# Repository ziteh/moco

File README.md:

# moco

|  SC1  | RD501 |
| :---: | :---: |
|  |  |

BLDC/PMSM motor controller/driver boards. [SC1 Demo video](https://youtu.be/PZ3AqAKdYeg)

- [SC1](/hardware/moco-sc1/): STSPIN32G4 + CSD88584Q5DC. Square PCB 40x40mm.
- [RD501](/hardware/moco-rd501/): DRV8301 + STM32G431. Square PCB 50x50mm.
- [RD321](/hardware/moco-rd321/): STSPIN32F0A + SiZ250DT. Square PCB 32x32mm.
- [OD501](/hardware/moco-od501/): DRV8323H + STM32G431. Round PCB Ø50mm.
- [OI401](/hardware/moco-oi401/): DRV8316C + STM32G431. Round PCB Ø40mm.
- [PG4](/hardware/moco-pg4/):  :construction: WIP.
- [BKD8316](/hardware/moco-bkd8316/): DRV8316 Breakout board

## Disclaimer & License

> [!WARNING]  
> None of the boards here are guaranteed to work.

These files are provided AS IS, without warranty of any kind.  
Including but not limited to manufacturing, assembly, procurement and use at your own risk.  
It is recommended to check yourself before use.  

For the full statement, please see license.  
Hardware licensed under the [CERN-OHL-P v2](/LICENSE-CERN-OHL-P), firmware licensed under the [MIT License](/LICENSE-MIT).

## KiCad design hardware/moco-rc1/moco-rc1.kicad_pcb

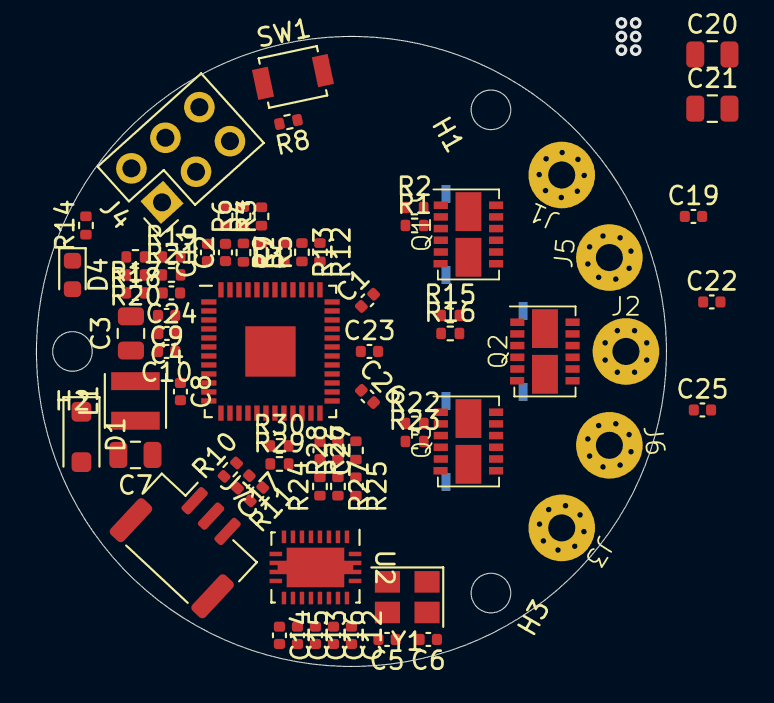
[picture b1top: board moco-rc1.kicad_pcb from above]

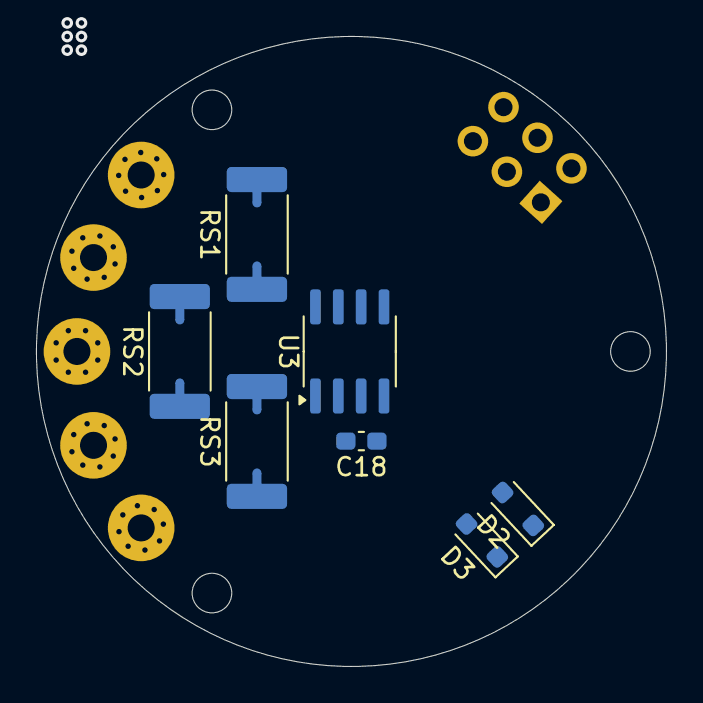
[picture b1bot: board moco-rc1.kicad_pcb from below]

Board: 4 copper layers, 35.0 x 35.0 mm, 89 parts (13 on the bottom side), 68 nets, no tracks yet.

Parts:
C1, C23, C26: 100nF/50V; C_0402_1005Metric
C2, C24, C27: 1nF; C_0402_1005Metric
C3, C20, C21: 10uF/50V; C_0805_2012Metric
C4, C14: 10nF; C_0402_1005Metric
C5, C6: 12pF; C_0402_1005Metric
C7: 47uF; C_0805_2012Metric
C8, C10, C11, C15, C16: 100nF; C_0402_1005Metric
C9, C13: 10uF; C_0402_1005Metric
C12: 300nF; C_0402_1005Metric
C17: 4.7nF; C_0402_1005Metric
C18: 100nF; C_0603_1608Metric_Pad1.08x0.95mm_HandSolder
C19, C22, C25: 220nF/50V; C_0402_1005Metric
D1: MBR180S1; D_SOD-123F
D2, D3: TVS; D_SOD-323_HandSoldering
D4: LED; LED_0603_1608Metric
H1, H2, H3: MountingHole; MountingHole_2.2mm_M2_ISO7380
J1: OUT_U; Conn_1x1_3.7_1.5
J2: OUT_V; Conn_1x1_3.7_1.5
J3: OUT_W; Conn_1x1_3.7_1.5
J4: Conn_02x03_Odd_Even; PinHeader_2x03_P2.54mm_Vertical
J5: VM+; Conn_1x1_3.7_1.5
J6: VM-; Conn_1x1_3.7_1.5
J7: CAN; JST_GH_SM03B-GHS-TB_1x03-1MP_P1.25mm_Horizontal
L1: 18uH; L_Neosid_SMS-ME3015
NT1, NT2, NT3, NT4, NT5, NT6: NetTie_2; NetTie-2_SMD_Pad0.5mm
Q1, Q2, Q3: FDMD8240LET40; PQFN-12
R1, R2, R15, R16, R22, R23: 10R; R_0402_1005Metric
R3, R6, R17, R20, R24, R27: 24k; R_0402_1005Metric
R4, R5, R18, R19, R25, R26: 1.78k; R_0402_1005Metric
R7, R21, R28: 12k; R_0402_1005Metric
R8, R9, R14, R30: 10k; R_0402_1005Metric
R10, R11: 60R; R_0402_1005Metric
R12, R13: 4.7k; R_0402_1005Metric
R29: 68k; R_0402_1005Metric
RS1, RS2, RS3: 20mΩ/3W; R_2512_6332Metric_Pad1.40x3.35mm_HandSolder
SW1: RESET; SW_SPST_B3U-1000P
U1: STSPIN32F0A; VFQFN-48_7x7_EP2.8mm_Pitch0.5mm
U2: TCAN4550; VQFN-20_3.5_3.5_0.5p
U3: AS5600; SOIC-8_3.9x4.9mm_P1.27mm
Y1: 40MHz; Crystal_SMD_3225-4Pin_3.2x2.5mm

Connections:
+3.3V: C7.1, C8.1, C11.1, C16.1, C18.2, J4.1, L1.1, R3.1, R8.1, R12.1, R13.1, R17.1, R24.1, U1.10 (VDDA), U1.48 (VDD), U2.17 (V_{IO}), U3.1 (VDD5V), U3.2 (VDD3V3)
+12V: C9.1, C15.1, U1.6 (VREG12), U2.14 (V_{SUP})
/BOOT0: R9.1, U1.42 (BOOT0)
/CAN Bus/5V_out: C13.1, U2.16 (V_{CCOUT})
/CAN Bus/CANH: D2.2 (A2), J7.1, R10.1, U2.11 (CANH)
/CAN Bus/CANL: D3.1 (A1), J7.3, R11.2, U2.10 (CANL)
/CAN Bus/OSC_IN: C5.2, U2.1 (OSC1), Y1.3
/CAN Bus/OSC_OUT: C6.1, U2.20 (OSC2), Y1.1
/I2C_SCL: R12.2, U1.40 (PB6), U3.7 (SCL)
/I2C_SDA: R13.2, U1.41 (PB7), U3.6 (SDA)
/Power Stage/OPA_U: C2.1, R7.2, U1.47 (OP3O)
/Power Stage/OPA_V: C24.1, R21.2, U1.3 (OP2O)
/Power Stage/OPA_W: C27.1, R28.2, U1.21 (OP1O)
/Power Stage/OUT_U: J1.1, Q1.7 (D2/S1), Q1.8 (D2/S1), Q1.9 (D2/S1), Q1.10 (D2/S1), Q1.14 (D2/S1)
/Power Stage/OUT_V: J2.1, Q2.7 (D2/S1), Q2.8 (D2/S1), Q2.9 (D2/S1), Q2.10 (D2/S1), Q2.14 (D2/S1)
/Power Stage/OUT_W: J3.1, Q3.7 (D2/S1), Q3.8 (D2/S1), Q3.9 (D2/S1), Q3.10 (D2/S1), Q3.14 (D2/S1)
/Power Stage/QGH_U: Q1.12 (G1), R2.2
/Power Stage/QGH_V: Q2.12 (G1), R15.2
/Power Stage/QGH_W: Q3.12 (G1), R22.2
/Power Stage/QGL_U: Q1.4 (G2), R1.2
/Power Stage/QGL_V: Q2.4 (G2), R16.2
/Power Stage/QGL_W: Q3.4 (G2), R23.2
/Power Stage/QO_U: C1.2, Q1.11 (G1R), U1.34 (OUTU)
/Power Stage/QO_V: C23.2, Q2.11 (G1R), U1.30 (OUTV)
/Power Stage/QO_W: C26.2, Q3.11 (G1R), U1.26 (OUTW)
/Power Stage/QS_U: NT1.1, Q1.5 (S2), Q1.6 (S2), RS1.1
/Power Stage/QS_V: NT3.1, Q2.5 (S2), Q2.6 (S2), RS2.1
/Power Stage/QS_W: NT5.1, Q3.5 (S2), Q3.6 (S2), RS3.1
/Power Stage/RS_U+: NT1.2, R18.1
/Power Stage/RS_U-: NT2.2, R19.1
/Power Stage/RS_V+: NT3.2, R4.1
/Power Stage/RS_V-: NT4.2, R5.1
/Power Stage/RS_W+: NT5.2, R25.1
/Power Stage/RS_W-: NT6.2, R26.1
/SPI_IRQ: U1.4 (PF0), U2.8 (~INT)
/SPI_MISO: U1.17 (PA6), U2.6 (SDO)
/SPI_MOSI: U1.18 (PA7), U2.5 (SDI)
/SPI_SCK: U1.16 (PA5), U2.4 (SCLK)
/SPI_~CS: U1.5 (PF1), U2.7 (~CS)
/SWC: J4.5, U1.38 (PA14_SWD_CLK)
/SWD: J4.3, U1.37 (PA13_SWD_IO)
/UART_RX: J4.6, U1.39 (PA15)
/UART_TX: J4.4, U1.13 (PA2)
/User_LED: D4.2 (A), U1.15 (PA4)
/VM_sense: R29.2, R30.1, U1.19 (PB1)
/~RESET: C4.1, R8.2, SW1.1, U1.7 (NRST)
GND: C3.2, C4.2, C5.1, C6.2, C7.2, C8.2, C9.2, C10.2, C11.2, C12.2, C13.2, C14.2, C15.2, C16.2, C17.2, C18.1, C19.2, C20.2, C21.2, C22.2, C25.2, D1.2 (A), D2.1 (A1), D3.2 (A2), J4.2, J6.1, J7.2, NT2.1, NT4.1, NT6.1, R6.2, R9.2, R14.2, R20.2, R27.2, R30.2, RS1.2, RS2.2, RS3.2, SW1.2, U1.20 (TESTMODE), U1.44 (GND), U1.49 (EPAD), U2.13 (GND), U3.4 (GND), Y1.2, Y1.4
unnamed: C17.1, R10.2, R11.1
unnamed: D1.1 (K), L1.2, U1.9 (SW)
unnamed: D4.1 (K), R14.1
unnamed: R22.1, U1.25 (HSW)
unnamed: R23.1, U1.28 (LSW)
unnamed: C26.1, U1.27 (VBOOTW)
unnamed: R15.1, U1.29 (HSV)
unnamed: R16.1, U1.32 (LSV)
unnamed: C23.1, U1.31 (VBOOTV)
unnamed: R2.1, U1.33 (HSU)
unnamed: R1.1, U1.36 (LSU)
unnamed: C1.1, U1.35 (VBOOTU)
unnamed: C2.2, R5.2, R7.1, U1.46 (OP3N)
unnamed: R3.2, R4.2, R6.1, U1.45 (OP3P)
unnamed: C24.2, R19.2, R21.1, U1.2 (OP2N)
unnamed: R17.2, R18.2, R20.1, U1.1 (OP2P)
unnamed: C27.2, R26.2, R28.1, U1.22 (OP1N)
unnamed: R24.2, R25.2, R27.1, U1.23 (OP1P)
unnamed: C12.1, U2.18 (FLTR)
unnamed: C14.1, U2.12 (WAKE)
VM: C3.1, C10.1, C19.1, C20.1, C21.1, C22.1, C25.1, J5.1, Q1.1 (D1), Q1.2 (D1), Q1.3 (D1), Q1.13 (D1), Q2.1 (D1), Q2.2 (D1), Q2.3 (D1), Q2.13 (D1), Q3.1 (D1), Q3.2 (D1), Q3.3 (D1), Q3.13 (D1), R29.1, U1.8 (VM)

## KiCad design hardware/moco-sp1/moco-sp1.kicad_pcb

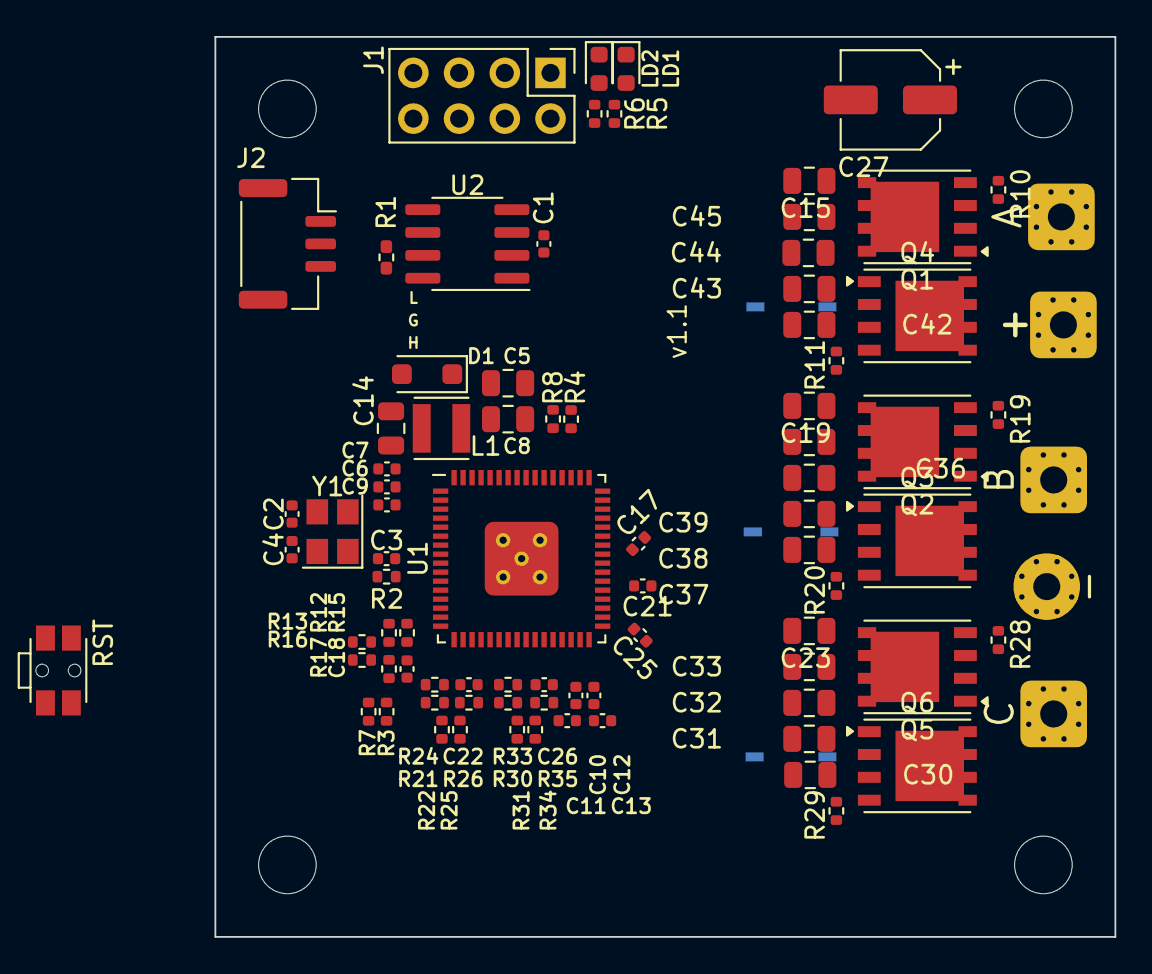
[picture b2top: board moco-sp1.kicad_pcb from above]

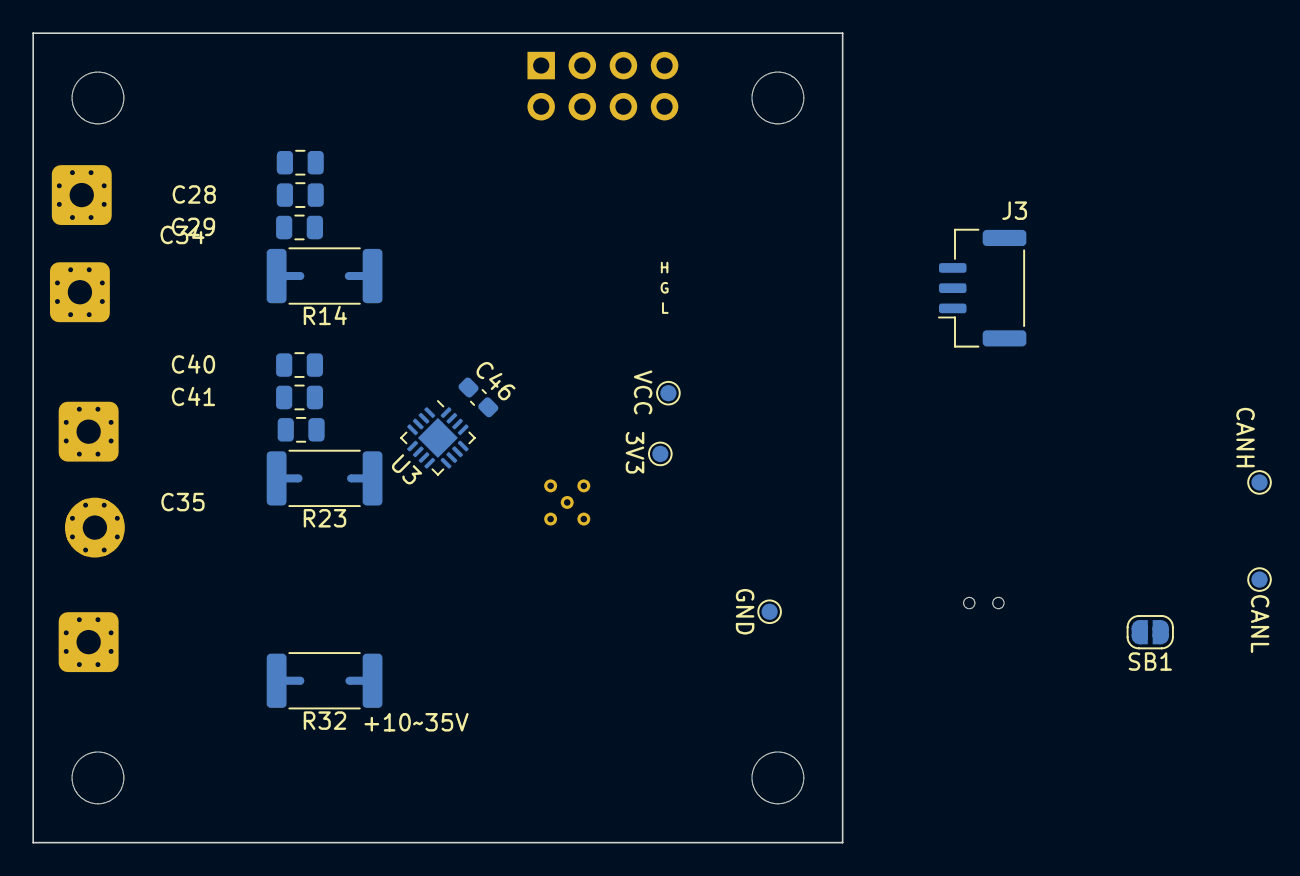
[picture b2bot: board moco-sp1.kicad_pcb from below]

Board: 4 copper layers, 50.0 x 50.0 mm, 115 parts (24 on the bottom side), 63 nets, no tracks yet.

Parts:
C1, C3, C6, C9, C10, C12: 100nF; C_0402_1005Metric
C2, C4: 6.8pF; C_0402_1005Metric
C5, C28, C29, C30, C31, C32, C33, C34, C35, C36, C37, C38, C39, C40, C41, C42, C43, C44, C45: 10uF/50V; C_0805_2012Metric
C7: 10uF; C_0402_1005Metric
C8, C15, C19, C23: 220nF/50V; C_0805_2012Metric
C11, C13: 1uF; C_0402_1005Metric
C14: 10uF; C_0805_2012Metric
C17, C21, C25: 100nF/50V; C_0402_1005Metric
C18, C22, C26: 1nF; C_0402_1005Metric
C27: 22uF/50V; CP_Elec_5x5.8
C46: 1uF; C_0603_1608Metric_Pad1.08x0.95mm_HandSolder
D1: MBR180S1; D_SOD-123F
H1, H2, H3, H4: MountingHole; MountingHole_3.2mm_M3_ISO14580
J1: Debug; PinHeader_2x04_P2.54mm_Vertical
J2, J3: CAN; JST_GH_SM03B-GHS-TB_1x03-1MP_P1.25mm_Horizontal
J4: V+; wire_rectagnel_3.7mm_D1.5mm
J5: V-; wire_circ_3.7mm_D1.5mm
J6: A; wire_rectagnel_3.7mm_D1.5mm
J7: B; wire_rectagnel_3.7mm_D1.5mm
J8: C; wire_rectagnel_3.7mm_D1.5mm
L1: 18uH; L_Neosid_SMS-ME3015
LD1: Red; LED_0603_1608Metric
LD2: Blue; LED_0603_1608Metric
NT1, NT2, NT3, NT4, NT5, NT6: NetTie_2; NetTie-2_SMD_Pad0.5mm
Q1, Q2, Q3, Q4, Q5, Q6: SiDR390DP; PowerPAK_SO-8_Single
R1: 120R; R_0402_1005Metric_Pad0.72x0.64mm_HandSolder
R2, R6, R7, R8: 10k; R_0402_1005Metric
R3: 100k; R_0402_1005Metric
R4: 22k; R_0402_1005Metric
R5: 1k; R_0402_1005Metric
R10, R11, R19, R20, R28, R29: 10R; R_0402_1005Metric
R12, R15, R21, R24, R30, R33: 24k; R_0402_1005Metric
R13, R16, R22, R25, R31, R34: 1.78k; R_0402_1005Metric
R14, R23, R32: 20mΩ/3W; R_2512_6332Metric
R17, R26, R35: 12k; R_0402_1005Metric
SB1: SolderJumper_2_Open; SolderJumper-2_P1.3mm_Open_RoundedPad1.0x1.5mm
SW1: RESET; SW_SPST_EVQP7C
TP1: CANH; TestPoint_Pad_D1.0mm
TP2: CANL; TestPoint_Pad_D1.0mm
TP3: 3.3V; TestPoint_Pad_D1.0mm
TP4: VCC; TestPoint_Pad_D1.0mm
TP5: GND; TestPoint_Pad_D1.0mm
U1: STSPIN32G4; VFQFPN 9X9X1.0 64 PITCH 0.5
U2: TCAN337; SOIC-8_3.9x4.9mm_P1.27mm
U3: MA702; QFN-16-1EP_3x3mm_P0.5mm_EP1.75x1.75mm
Y1: 16MHz; Crystal_SMD_3225-4Pin_3.2x2.5mm
kibuzzard-64C58EFF: G***; kibuzzard-64C58EFF

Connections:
+3.3V: C1.2, C6.2, C7.2, C9.2, C10.2, C11.2, C12.2, C13.2, C46.2, J1.1, R2.2, R4.1, R12.1, R21.1, R30.1, TP3.1, U1.1 (REG3V3/VDD), U1.2 (VBAT), U1.26 (VREF+), U1.27 (VDDA), U2.3 (VCC), U3.13 (VDD)
/CANH: J2.3, J3.3, SB1.1 (A), TP1.1, U2.7 (CANH)
/CANL: J2.1, J3.1, R1.2, TP2.1, U2.6 (CANL)
/CAN_RX: U1.47 (PA11), U2.4 (RXD)
/CAN_TX: U1.48 (PA12), U2.1 (TXD)
/OPAMP1_VINM: C18.2, R16.2, R17.1, U1.16 (PA3)
/OPAMP1_VINP: R12.2, R13.2, R15.1, U1.14 (PA1)
/OPAMP1_VOUT: C18.1, R17.2, U1.15 (PA2)
/OPAMP2_VINM: C22.2, R25.2, R26.1, U1.22 (PC5)
/OPAMP2_VINP: R21.2, R22.2, R24.1, U1.20 (PA7)
/OPAMP2_VOUT: C22.1, R26.2, U1.19 (PA6)
/OPAMP3_VINM: C26.2, R34.2, R35.1, U1.25 (PB2)
/OPAMP3_VINP: R30.2, R31.2, R33.1, U1.23 (PB0)
/OPAMP3_VOUT: C26.1, R35.2, U1.24 (PB1)
/OSC_IN: C2.2, U1.6 (PF0), Y1.3
/OSC_OUT: C4.2, U1.7 (PF1), Y1.1
/Power Stage/OUTA: C17.1, J6.1, Q1.1 (S), Q1.2 (S), Q1.3 (S), Q4.5 (D), U1.42 (OUT1)
/Power Stage/OUTB: C21.1, J7.1, Q2.1 (S), Q2.2 (S), Q2.3 (S), Q3.5 (D), U1.39 (OUT2)
/Power Stage/OUTC: C25.1, J8.1, Q5.1 (S), Q5.2 (S), Q5.3 (S), Q6.5 (D), U1.36 (OUT3)
/Power Stage/RSA+: NT1.1, R13.1
/Power Stage/RSA-: NT2.1, R16.1
/Power Stage/RSB+: NT3.1, R22.1
/Power Stage/RSB-: NT4.1, R25.1
/Power Stage/RSC+: NT5.1, R31.1
/Power Stage/RSC-: NT6.1, R34.1
/Power Stage/S2A: NT1.2, Q4.1 (S), Q4.2 (S), Q4.3 (S), R14.1
/Power Stage/S2B: NT3.2, Q3.1 (S), Q3.2 (S), Q3.3 (S), R23.1
/Power Stage/S2C: NT5.2, Q6.1 (S), Q6.2 (S), Q6.3 (S), R32.1
/SCREF: R4.2, R8.1, U1.52 (SCREF)
/SPI_MISO: U1.55 (PB4), U3.7 (MISO)
/SPI_MOSI: U1.56 (PB5), U3.4 (MOSI)
/SPI_SCLK: U1.54 (PB3), U3.12 (SCLK)
/SPI_~CS_RS: U1.57 (PB6), U3.5 (~CS)
/SWCLK: J1.5, U1.50 (PA14)
/SWDIO: J1.3, U1.49 (PA13)
/SWO: J1.7, U1.51 (PA15)
/USART_RX: J1.6, U1.46 (PA10)
/USART_TX: J1.4, U1.45 (PA9)
/USER_LED: R5.1, U1.13 (PA0)
/V_{BUS}_SENSE: R3.1, R7.2, U1.17 (PA4)
/~RESET: C3.1, R2.1, SW1.1, U1.8 (PG10)
GND: C1.1, C2.1, C3.2, C4.1, C5.2, C6.1, C7.1, C8.2, C9.1, C10.1, C11.1, C12.1, C13.1, C14.2, C15.1, C19.1, C23.1, C27.2, C28.2, C29.2, C30.2, C31.2, C32.2, C33.2, C34.2, C35.2, C36.2, C37.2, C38.2, C39.2, C40.2, C41.2, C42.2, C43.2, C44.2, C45.2, C46.1, D1.2 (A), J1.2, J1.8, J2.2, J3.2, J5.1, LD1.1 (K), LD2.1 (K), NT2.2, NT4.2, NT6.2, R7.1, R8.2, R14.2, R15.2, R23.2, R24.2, R32.2, R33.2, SW1.2, TP5.1, U1.32 (PGND), U1.59 (PB8), U1.65 (VSS), U2.2 (GND), U3.8 (GND), U3.10 (TEST), U3.17 (PAD), Y1.2, Y1.4
unnamed: D1.1 (K), L1.1, U1.62 (SW)
unnamed: LD1.2 (A), R5.2
unnamed: LD2.2 (A), R6.2
unnamed: Q1.4 (G), R10.2
unnamed: Q2.4 (G), R19.2
unnamed: Q3.4 (G), R20.2
unnamed: Q4.4 (G), R11.2
unnamed: Q5.4 (G), R28.2
unnamed: Q6.4 (G), R29.2
unnamed: R1.1, SB1.2 (B)
unnamed: C17.2, U1.41 (BOOT1)
unnamed: R10.1, U1.43 (GHS1)
unnamed: R11.1, U1.29 (GLS1)
unnamed: C21.2, U1.38 (BOOT2)
unnamed: R19.1, U1.40 (GHS2)
unnamed: R20.1, U1.30 (GLS2)
unnamed: C25.2, U1.35 (BOOT3)
unnamed: R28.1, U1.37 (GHS3)
unnamed: R29.1, U1.31 (GLS3)
VBUS: C5.1, C8.1, C15.2, C19.2, C23.2, C27.1, C28.1, C29.1, C30.1, C31.1, C32.1, C33.1, C34.1, C35.1, C36.1, C37.1, C38.1, C39.1, C40.1, C41.1, C42.1, C43.1, C44.1, C45.1, J4.1, Q1.5 (D), Q2.5 (D), Q5.5 (D), R3.2, U1.61 (VM)
VCC: C14.1, L1.2, R6.1, TP4.1, U1.63 (VCC), U1.64 (REGIN)

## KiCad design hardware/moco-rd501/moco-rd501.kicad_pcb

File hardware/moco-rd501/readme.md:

# moco-RD501

STM32G431C8T6 MCU, DRV8301 gate driver, CSD18540Q5B power N-MOSFETs and AS5047x magnetic encoder.

Based on [ODrive](https://github.com/odriverobotics/ODriveHardware) `v3.5` PCB and [SimpleFOC](https://simplefoc.com/) firmware.

> Seems unstable.

| Front                                | Back                                 | Layers                               |
| ------------------------------------ | ------------------------------------ | ------------------------------------ |
|  |  |  |

### Pinmap

| Description            | STM32 Pin |
| ---------------------- | --------- |
| PWM-A High             | PA8       |
| PWM-B High             | PA9       |
| PWM-C High             | PA10      |
| PWM-A Low              | PC13      |
| PWM-B Low              | PA12      |
| PWM-C Low              | PB15      |
| EN_Gate (Enable)       | PB3       |
| nFAULT                 | PB10      |
| Encoder A              | PB5       |
| Encoder B              | PB6       |
| Encoder I              | PB4       |
| SPI SCLK               | PA5       |
| SPI MISO               | PA6       |
| SPI MOSI               | PA7       |
| SPI nCS DRV8301        | PB13      |
| SPI nCS AS5047x        | PB14      |
| SPI nCS CAN-Bus        | PB9       |
| CAN-Bus INT            | PA11      |
| USART Tx               | PA2       |
| USART Rx               | PA3       |
| I2C SCL                | PA15      |
| I2C SDA                | PB7       |
| Current sense 1 (CH-B) | PA0       |
| Current sense 2 (CH-C) | PA1       |
| Temperature sense      | PA4       |
| V_drive sense          | PB12      |
| User LED 1 (Red)       | PB0       |
| User LED 2 (Blue)      | PB1       |
| GPIO PB2               | PB2       |
| GPIO PB11              | PB11      |

### Board Characteristics

- Copper layer count: 4
- Board overall dimensions: 50 x 50 mm
- Min track/spacing: 0.2 mm / 0.2 mm
- Min hole diameter: 0.2 mm
- Castellated pads: No
- Edge card connectors: No
- Plated board edge: No

Support JLCPCB's PCBA service.

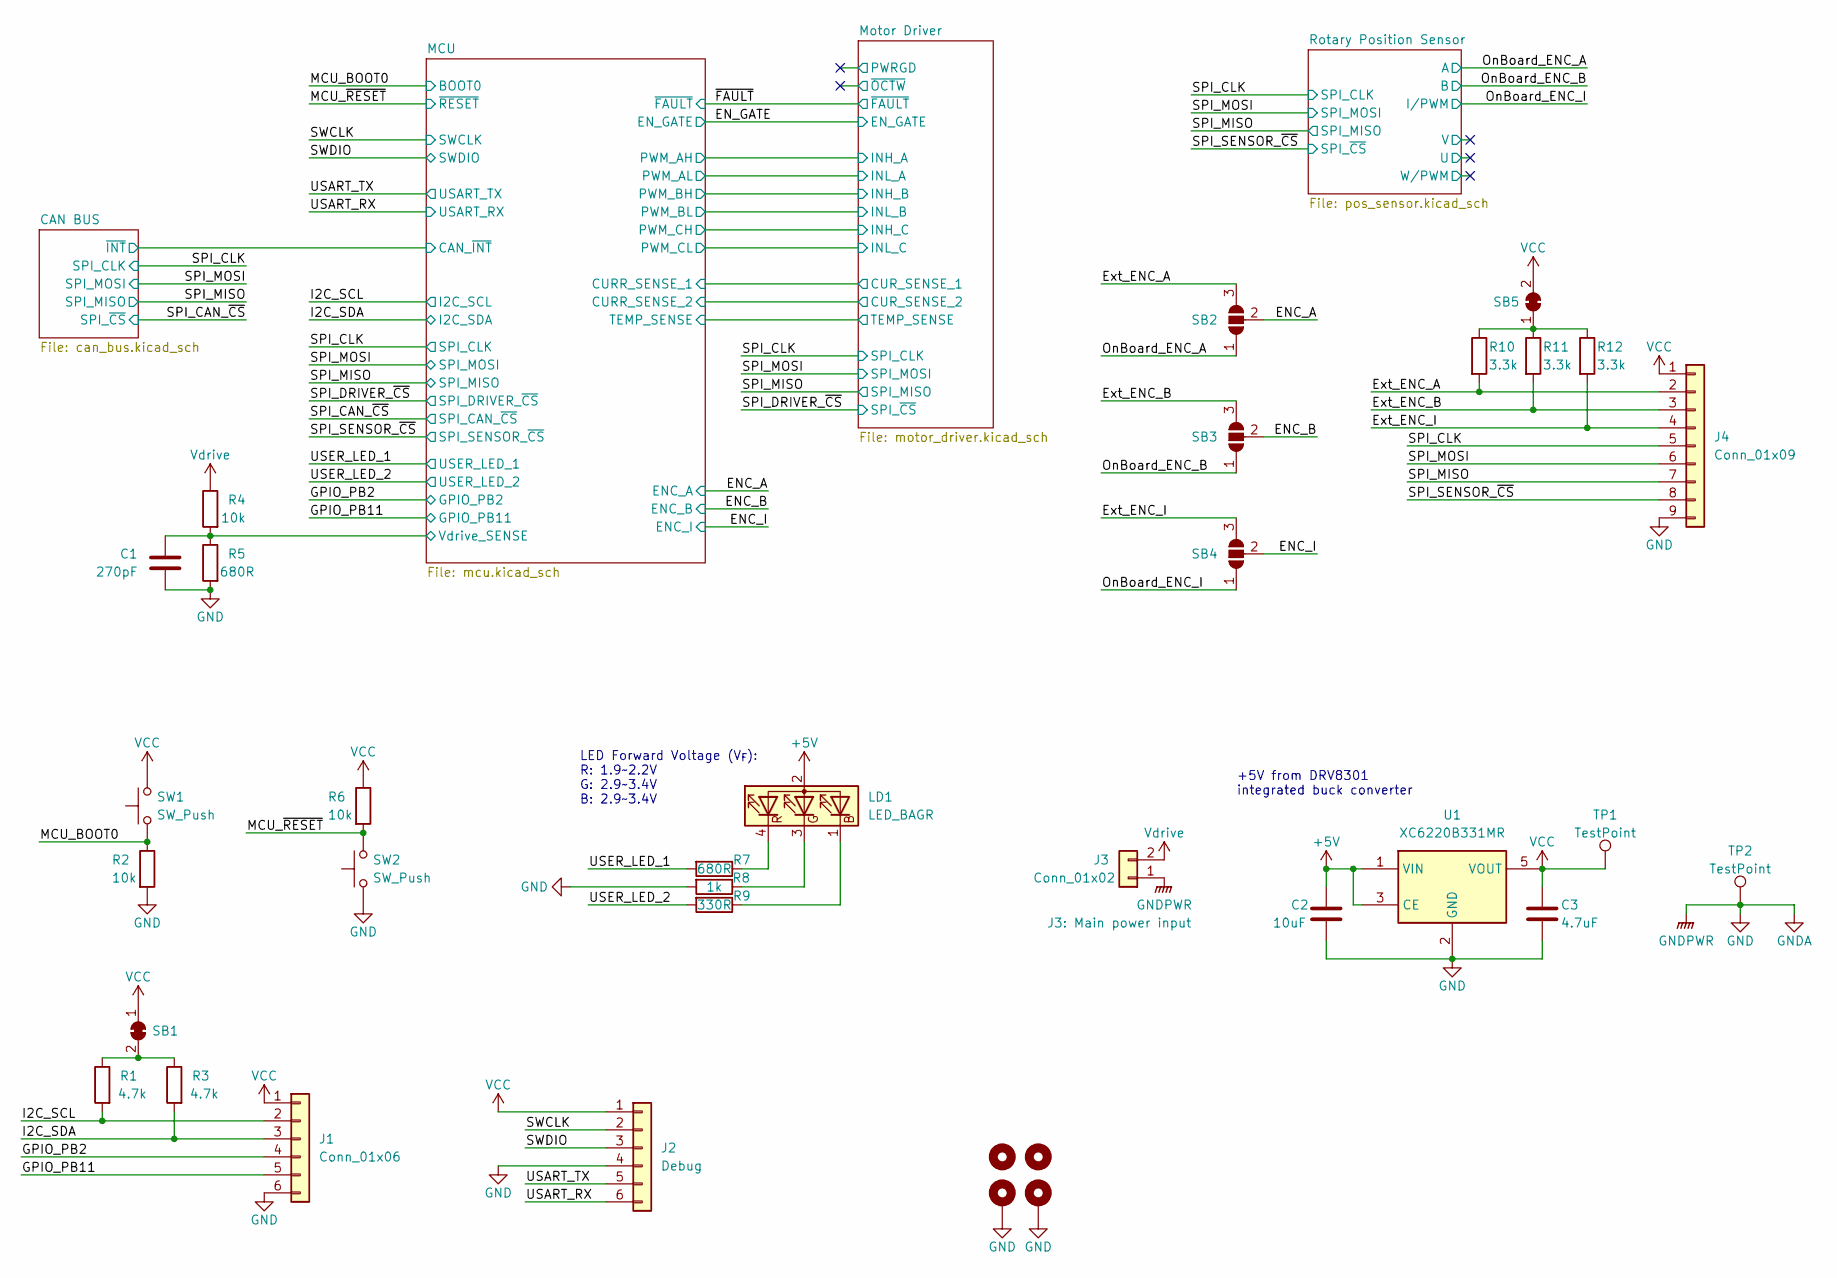
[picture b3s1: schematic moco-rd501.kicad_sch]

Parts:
C1: 270pF; C_0402_1005Metric; MFR.Part # GCM1555C1H271JA16D; JLCPCB Part # C524551
C2: 10uF; C_0402_1005Metric; MFR.Part # CL05A106MQ5NUNC; JLCPCB Part # C15525
C3: 4.7uF; C_0402_1005Metric; MFR.Part # CL05A475MP5NRNC; JLCPCB Part # C23733
H1, H3: MountingHole; MountingHole_2.2mm_M2_ISO14580
H2, H4: MountingHole_Pad; MountingHole_2.2mm_M2_Pad_Via
J1: Conn_01x06; JST_GH_SM06B-GHS-TB_1x06-1MP_P1.25mm_Horizontal; MFR.Part # GH1.25-6PWBPZ; JLCPCB Part # C2829255
J2: Debug; PinHeader_1x06_P2.54mm_Vertical
J3: Conn_01x02; AMASS_XT60-M_1x02_P7.20mm_Vertical; MFR.Part # XT60; JLCPCB Part # C98733
J4: Conn_01x09; JST_GH_SM09B-GHS-TB_1x09-1MP_P1.25mm_Horizontal; MFR.Part # GH1.25-9PWBPZ; JLCPCB Part # C2829258
LD1: LED_BAGR; RGB LED 1.6x1.6mm; MFR.Part # E6C0606RGBC3UDA; JLCPCB Part # C375569
R1, R3: 4.7k; R_0402_1005Metric; MFR.Part # 0402WGF4701TCE; JLCPCB Part # C25900
R2, R4, R6: 10k; R_0402_1005Metric; MFR.Part # 0402WGF1002TCE; JLCPCB Part # C25744
R5, R7: 680R; R_0402_1005Metric; MFR.Part # 0402WGF6800TCE; JLCPCB Part # C25130
R8: 1k; R_0402_1005Metric; MFR.Part # 0402WGF1001TCE; JLCPCB Part # C11702
R9: 330R; R_0402_1005Metric; MFR.Part # 0402WGF3300TCE; JLCPCB Part # C25104
R10, R11, R12: 3.3k; R_0402_1005Metric; MFR.Part # 0402WGF3301TCE; JLCPCB Part # C25890
SB1, SB5: SolderJumper_2_Bridged; SolderJumper-2_P1.3mm_Bridged_RoundedPad1.0x1.5mm
SB2, SB3, SB4: Jumper_3_Bridged12; SolderJumper-3_P1.3mm_Open_RoundedPad1.0x1.5mm_NumberLabels
SW1, SW2: SW_Push; SW_SPST_CK_RS282G05A3; MFR.Part # TS-1092S-B3D2-G; JLCPCB Part # C520860
TP1, TP2: TestPoint; TestPoint_Pad_D2.0mm
U1: XC6220B331MR; SOT-23-5; MFR.Part # XC6220B331MR-G; JLCPCB Part # C86534

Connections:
+5V: C2.1, LD1.2 (A), U1.1 (VIN), U1.3 (CE); also elsewhere on the board
/ENC_A: SB2.2 (C); also elsewhere on the board
/ENC_B: SB3.2 (C); also elsewhere on the board
/ENC_I: SB4.2 (C); also elsewhere on the board
/Ext_ENC_A: J4.2, R10.2, SB2.3 (B)
/Ext_ENC_B: J4.3, R11.2, SB3.3 (B)
/Ext_ENC_I: J4.4, R12.2, SB4.3 (B)
/GPIO_PB2: J1.4; also elsewhere on the board
/GPIO_PB11: J1.5; also elsewhere on the board
/I2C_SCL: J1.2, R1.2; also elsewhere on the board
/I2C_SDA: J1.3, R3.2; also elsewhere on the board
/MCU/Vdrive_SENSE: C1.1, R4.2, R5.1; also elsewhere on the board
/MCU_BOOT0: R2.1, SW1.1; also elsewhere on the board
/MCU_~RESET: R6.2, SW2.2; also elsewhere on the board
/OnBoard_ENC_A: SB2.1 (A); also elsewhere on the board
/OnBoard_ENC_B: SB3.1 (A); also elsewhere on the board
/OnBoard_ENC_I: SB4.1 (A); also elsewhere on the board
/SPI_CLK: J4.5; also elsewhere on the board
/SPI_MISO: J4.7; also elsewhere on the board
/SPI_MOSI: J4.6; also elsewhere on the board
/SPI_SENSOR_~CS: J4.8; also elsewhere on the board
/SWCLK: J2.2; also elsewhere on the board
/SWDIO: J2.3; also elsewhere on the board
/USART_RX: J2.6; also elsewhere on the board
/USART_TX: J2.5; also elsewhere on the board
/USER_LED_1: R7.2; also elsewhere on the board
/USER_LED_2: R9.2; also elsewhere on the board
GND: C1.2, C2.2, C3.2, H2.1, H4.1, J1.6, J2.4, J3.1, J4.9, R2.2, R5.2, R8.2, SW2.1, TP2.1, U1.2 (GND); also elsewhere on the board
unnamed: LD1.1 (BK), R9.1
unnamed: LD1.3 (GK), R8.1
unnamed: LD1.4 (RK), R7.1
unnamed: R1.1, R3.1, SB1.2 (B)
unnamed: R10.1, R11.1, R12.1, SB5.1 (A)
VCC: C3.1, J1.1, J2.1, J4.1, R6.1, SB1.1 (A), SB5.2 (B), SW1.2, TP1.1, U1.5 (VOUT); also elsewhere on the board
Vdrive: J3.2, R4.1; also elsewhere on the board

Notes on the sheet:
LED Forward Voltage (V_{F}): R: 1.9~2.2V G: 2.9~3.4V B: 2.9~3.4V
+5V from DRV8301 integrated buck converter

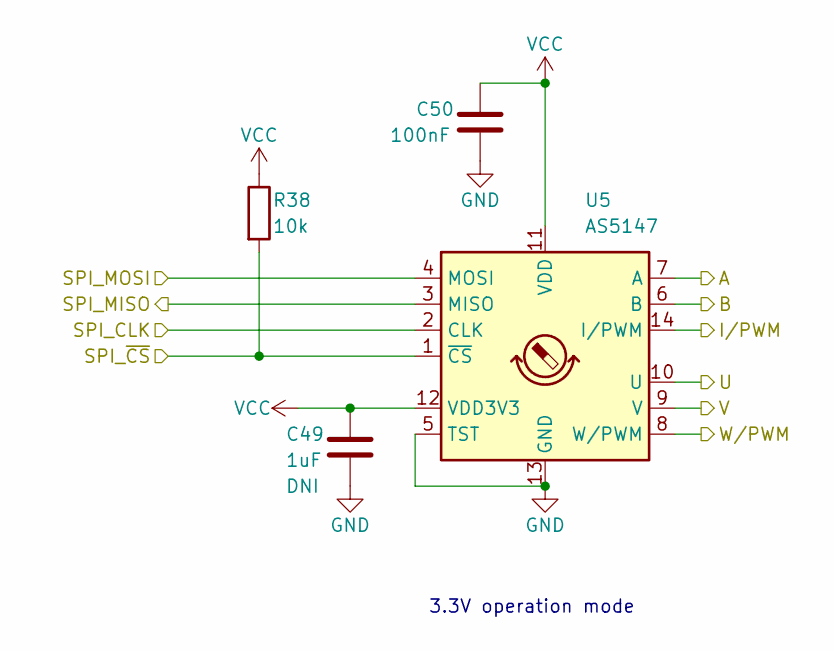
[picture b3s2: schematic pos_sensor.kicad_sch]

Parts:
C49: 1uF; C_0603_1608Metric
C50: 100nF; C_0603_1608Metric
R38: 10k; R_0402_1005Metric; MFR.Part # 0402WGF1002TCE; JLCPCB Part # C25744
U5: AS5147; TSSOP-14_4.4x5mm_P0.65mm; MFR.Part # AS5147P-HTSM; JLCPCB Part # C481876

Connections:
/OnBoard_ENC_A: U5.7 (A); also elsewhere on the board
/OnBoard_ENC_B: U5.6 (B); also elsewhere on the board
/OnBoard_ENC_I: U5.14 (I/PWM); also elsewhere on the board
/Rotary Position Sensor/U: U5.10 (U)
/Rotary Position Sensor/V: U5.9 (V)
/Rotary Position Sensor/W/PWM: U5.8 (W/PWM)
/SPI_CLK: U5.2 (CLK); also elsewhere on the board
/SPI_MISO: U5.3 (MISO); also elsewhere on the board
/SPI_MOSI: U5.4 (MOSI); also elsewhere on the board
/SPI_SENSOR_~CS: R38.2, U5.1 (~CS); also elsewhere on the board
GND: C49.2, C50.2, U5.5 (TST), U5.13 (GND); also elsewhere on the board
VCC: C49.1, C50.1, R38.1, U5.11 (VDD), U5.12 (VDD3V3); also elsewhere on the board

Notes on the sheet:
3.3V operation mode

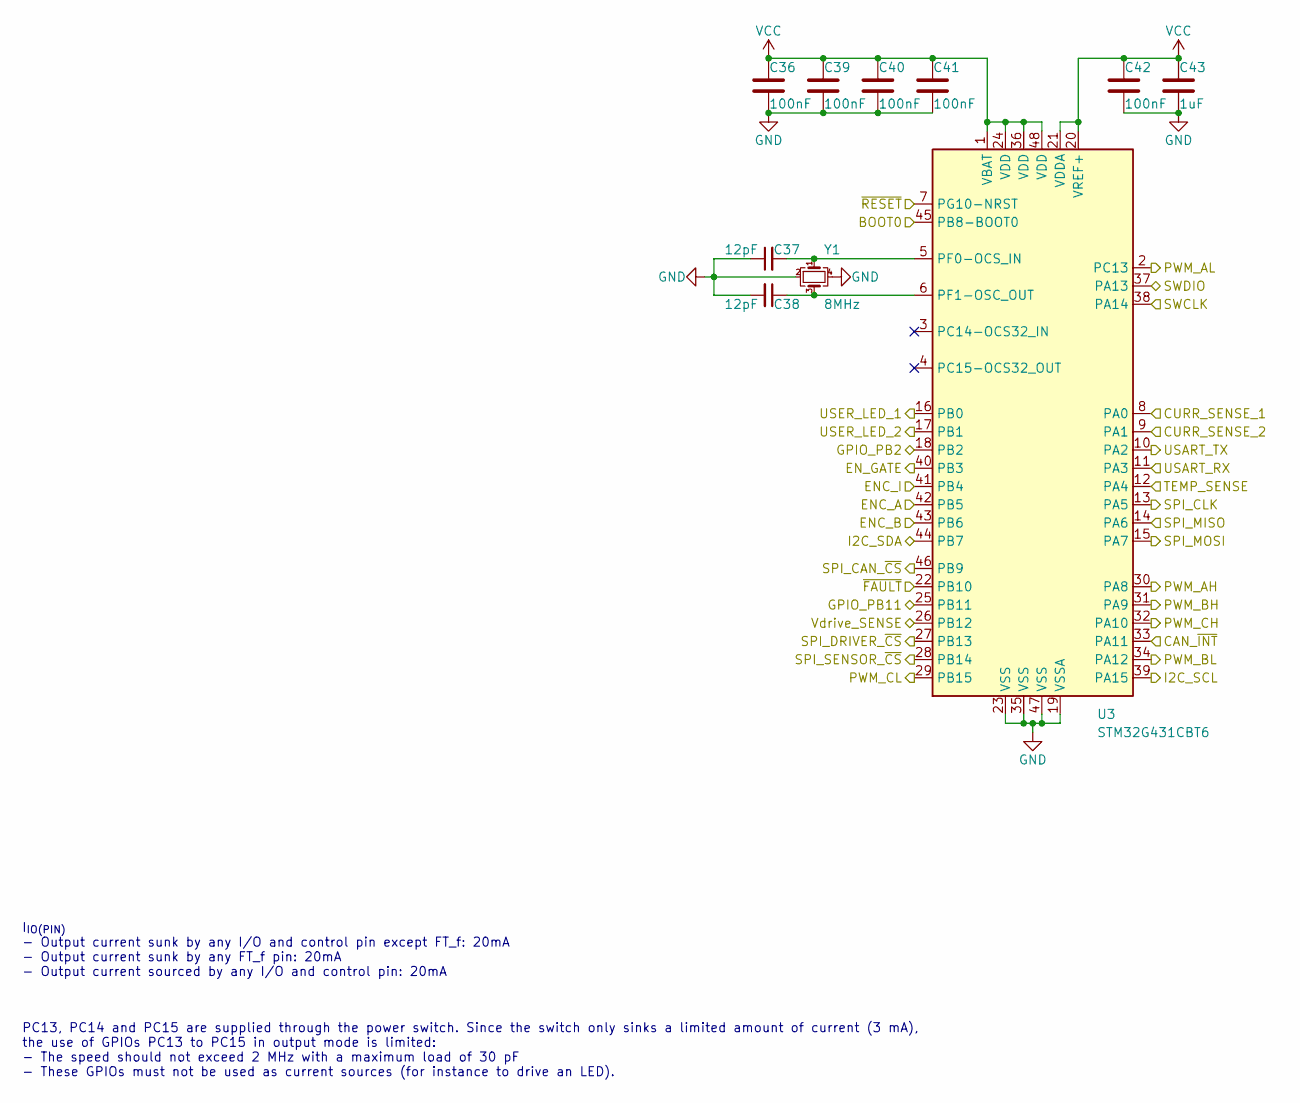
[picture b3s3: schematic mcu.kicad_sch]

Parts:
C36, C39, C40, C41, C42: 100nF; C_0402_1005Metric; MFR.Part # CL05B104KO5NNNC; JLCPCB Part # C1525
C37, C38: 12pF; C_0402_1005Metric; MFR.Part # 0402CG120J500NT; JLCPCB Part # C1547
C43: 1uF; C_0402_1005Metric; MFR.Part # CL05A105KA5NQNC; JLCPCB Part # C52923
U3: STM32G431CBT6; LQFP-48_7x7mm_P0.5mm; MFR.Part # STM32G431CBT6; JLCPCB Part # C529355
Y1: 8MHz; Crystal_SMD_3225-4Pin_3.2x2.5mm; MFR.Part # 1C208000BC0R; JLCPCB Part # C57131

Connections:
/CAN BUS/~INT: U3.33 (PA11); also elsewhere on the board
/ENC_A: U3.42 (PB5); also elsewhere on the board
/ENC_B: U3.43 (PB6); also elsewhere on the board
/ENC_I: U3.41 (PB4); also elsewhere on the board
/EN_GATE: U3.40 (PB3); also elsewhere on the board
/GPIO_PB2: U3.18 (PB2); also elsewhere on the board
/GPIO_PB11: U3.25 (PB11); also elsewhere on the board
/I2C_SCL: U3.39 (PA15); also elsewhere on the board
/I2C_SDA: U3.44 (PB7); also elsewhere on the board
/MCU/CURR_SENSE_1: U3.8 (PA0); also elsewhere on the board
/MCU/CURR_SENSE_2: U3.9 (PA1); also elsewhere on the board
/MCU/PWM_AH: U3.30 (PA8); also elsewhere on the board
/MCU/PWM_AL: U3.2 (PC13); also elsewhere on the board
/MCU/PWM_BH: U3.31 (PA9); also elsewhere on the board
/MCU/PWM_BL: U3.34 (PA12); also elsewhere on the board
/MCU/PWM_CH: U3.32 (PA10); also elsewhere on the board
/MCU/PWM_CL: U3.29 (PB15); also elsewhere on the board
/MCU/TEMP_SENSE: U3.12 (PA4); also elsewhere on the board
/MCU/Vdrive_SENSE: U3.26 (PB12); also elsewhere on the board
/MCU_BOOT0: U3.45 (PB8-BOOT0); also elsewhere on the board
/MCU_~RESET: U3.7 (PG10-NRST); also elsewhere on the board
/SPI_CAN_~CS: U3.46 (PB9); also elsewhere on the board
/SPI_CLK: U3.13 (PA5); also elsewhere on the board
/SPI_DRIVER_~CS: U3.27 (PB13); also elsewhere on the board
/SPI_MISO: U3.14 (PA6); also elsewhere on the board
/SPI_MOSI: U3.15 (PA7); also elsewhere on the board
/SPI_SENSOR_~CS: U3.28 (PB14); also elsewhere on the board
/SWCLK: U3.38 (PA14); also elsewhere on the board
/SWDIO: U3.37 (PA13); also elsewhere on the board
/USART_RX: U3.11 (PA3); also elsewhere on the board
/USART_TX: U3.10 (PA2); also elsewhere on the board
/USER_LED_1: U3.16 (PB0); also elsewhere on the board
/USER_LED_2: U3.17 (PB1); also elsewhere on the board
/~FAULT: U3.22 (PB10); also elsewhere on the board
GND: C36.2, C37.1, C38.2, C39.2, C40.2, C41.2, C42.2, C43.2, U3.19 (VSSA), U3.23 (VSS), U3.35 (VSS), U3.47 (VSS), Y1.2, Y1.4; also elsewhere on the board
unnamed: C37.2, U3.5 (PF0-OCS_IN), Y1.1
unnamed: C38.1, U3.6 (PF1-OSC_OUT), Y1.3
VCC: C36.1, C39.1, C40.1, C41.1, C42.1, C43.1, U3.1 (VBAT), U3.20 (VREF+), U3.21 (VDDA), U3.24 (VDD), U3.36 (VDD), U3.48 (VDD); also elsewhere on the board

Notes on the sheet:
I_{IO(PIN)} - Output current sunk by any I/O and control pin except FT_f: 20mA - Output current sunk by any FT_f pin: 20mA - Output current sourced by any I/O and control pin: 20mA
PC13, PC14 and PC15 are supplied through the power switch. Since the switch only sinks a limited amount of current (3 mA), the use of GPIOs PC13 to PC15 in output mode is limited: - The speed should not exceed 2 MHz with a maximum load of 30 pF - These GPIOs must not be used as current sources (for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

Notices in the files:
hardware/moco-drv8316/moco-oi401.kicad_pcb:
MIT license (Open source hardware)
hardware/moco-oi401/moco-oi401.kicad_pcb:
Open source hardware, CERN-OHL-P v2
